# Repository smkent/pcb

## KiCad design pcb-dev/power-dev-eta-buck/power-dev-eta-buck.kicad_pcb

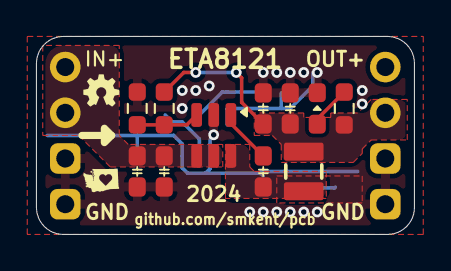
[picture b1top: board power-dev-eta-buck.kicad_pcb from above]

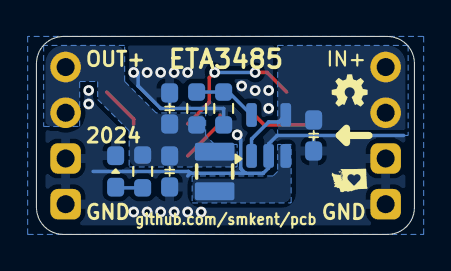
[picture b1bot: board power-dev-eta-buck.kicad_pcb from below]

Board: 2 copper layers, 21.0 x 11.0 mm, 22 parts (11 on the bottom side), 10 nets.

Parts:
C0, C1, C4: 10u; C_0603_1608Metric_Pad1.08x0.95mm_HandSolder
C2, C3, C5, C6: 22u; C_0603_1608Metric_Pad1.08x0.95mm_HandSolder
C7: 10n; C_0603_1608Metric_Pad1.08x0.95mm_HandSolder
J1, J2: Pin headers; PinHeader_1x04_P2.54mm_Vertical_simple_pad3,4gnd
L1, L2: 4u7; IND-SMD_L2.5-W2.0_MHCHL2520
LED1, LED2: LED_Small; LED_0603_1608Metric_Pad1.05x0.95mm_HandSolder_simple
R1: 56K; R_0603_1608Metric_Pad0.98x0.95mm_HandSolder
R2, R3, R5, R6: 10K; R_0603_1608Metric_Pad0.98x0.95mm_HandSolder
R4: 75K; R_0603_1608Metric_Pad0.98x0.95mm_HandSolder
U1: ETA8121; SOT-23-6_simple
U2: ETA3485; SOT-23-5_simple

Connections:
/SW_B: L2.1, U2.3 (SW)
/SW_F: C7.2, L1.1, U1.6 (SW)
FB_B: R4.1, R5.2, U2.5 (FB)
FB_F: R1.1, R2.2, U1.3 (FB)
GND: C0.2, C1.2, C2.2, C3.2, C4.2, C5.2, C6.2, J1.3, J1.4, J2.3, J2.4, LED1.1 (K), LED2.1 (K), R2.1, R5.1, U1.2 (GND), U2.2 (GND)
unnamed: LED1.2 (A), R3.1
unnamed: LED2.2 (A), R6.1
unnamed: C7.1, U1.1 (BST)
VIN: C0.1, C1.1, C4.1, J1.1, J1.2, U1.4 (EN), U1.5 (VIN), U2.1 (EN), U2.4 (IN)
VOUT: C2.1, C3.1, C5.1, C6.1, J2.1, J2.2, L1.2, L2.2, R1.2, R3.2, R4.2, R6.2

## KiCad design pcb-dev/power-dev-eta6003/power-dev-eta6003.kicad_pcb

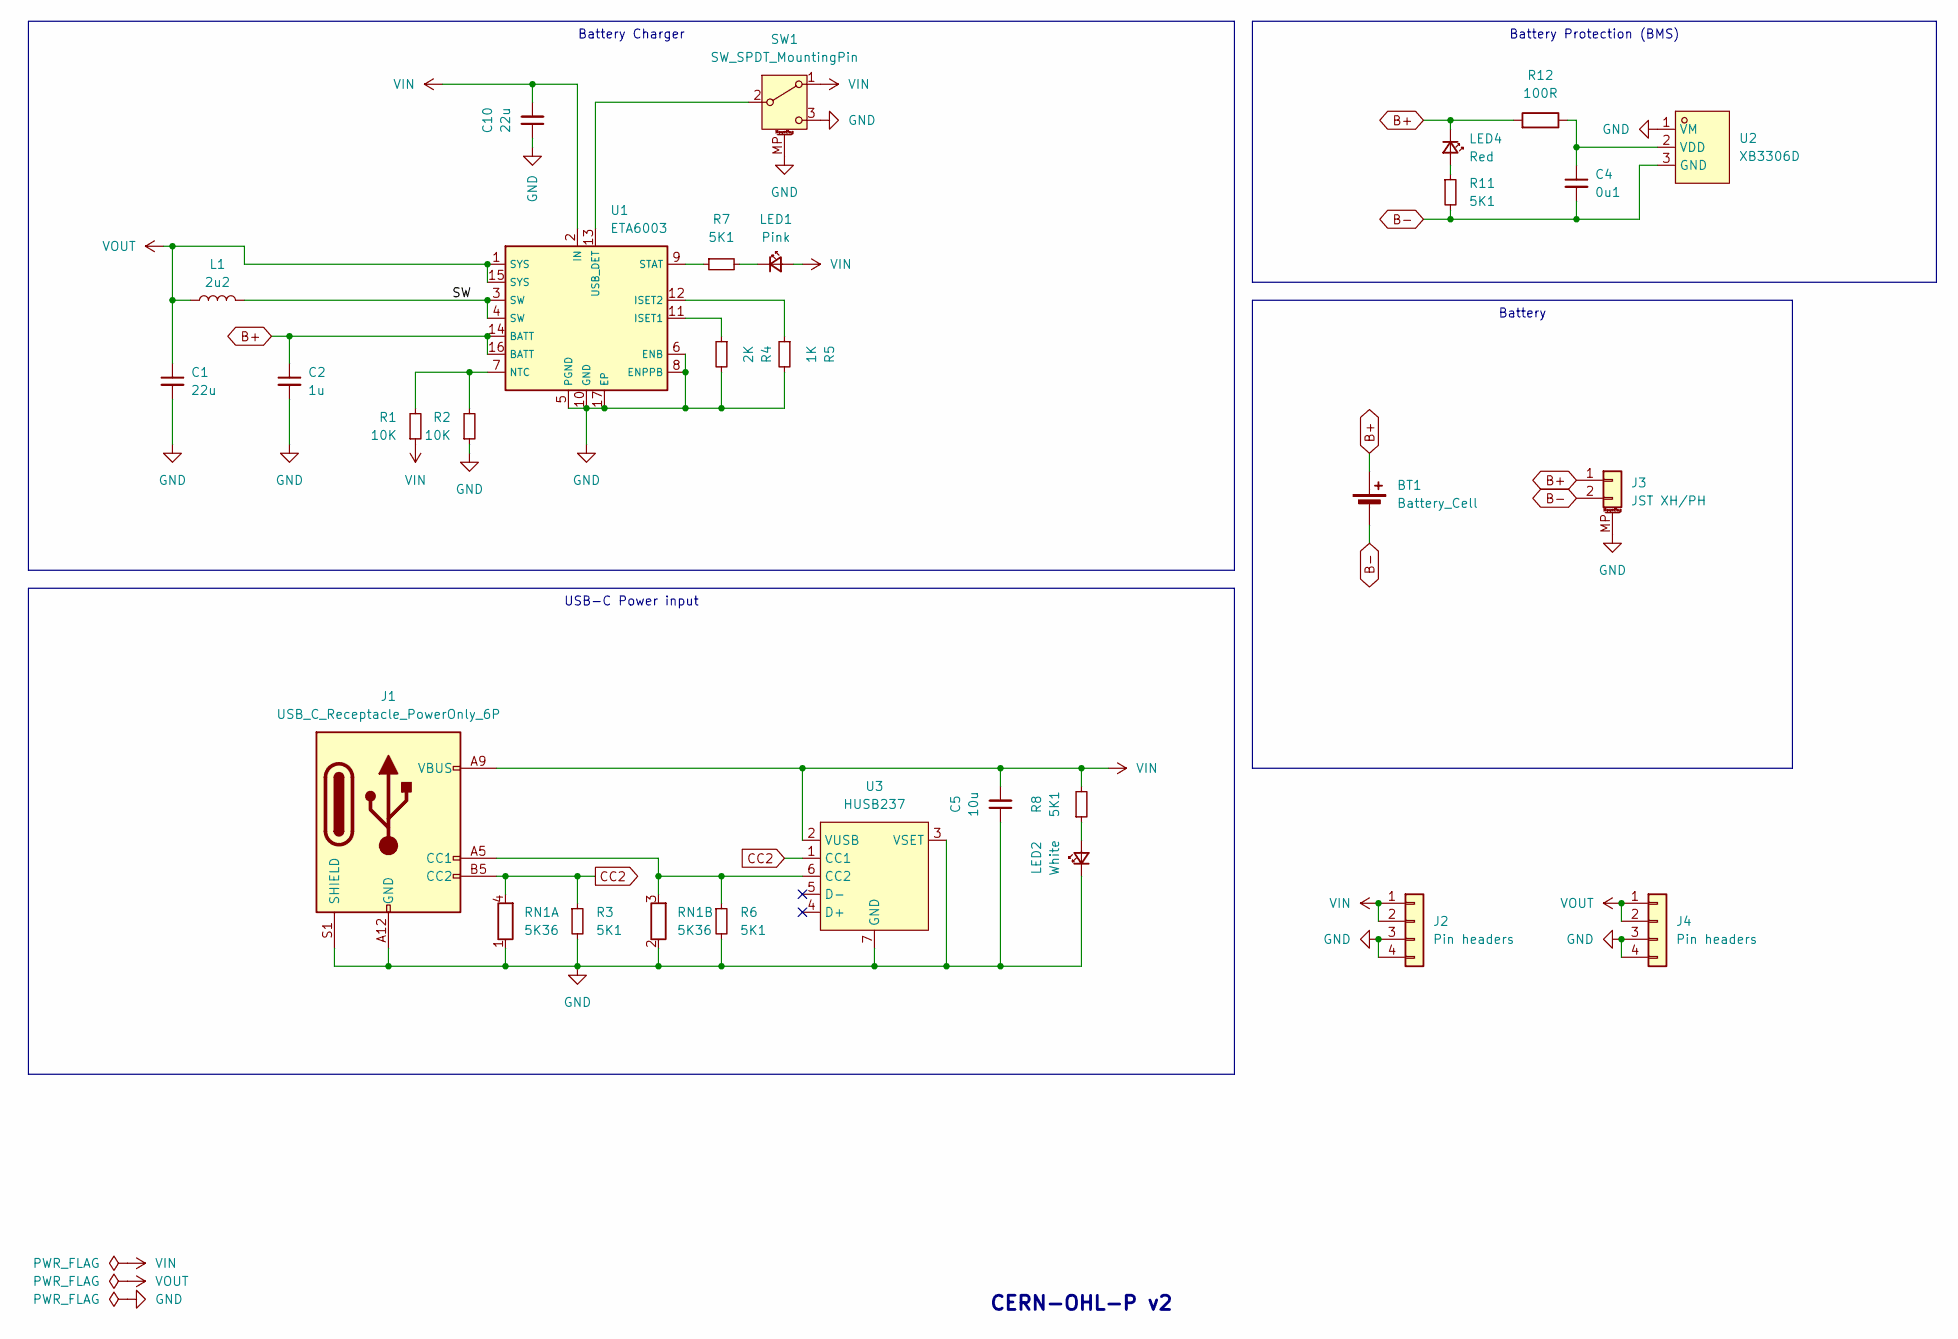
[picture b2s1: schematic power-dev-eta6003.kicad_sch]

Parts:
BT1: Battery_Cell; BAT-TH_18650-A5BJ001
C1: 22u; C_0603_1608Metric_Pad1.08x0.95mm_HandSolder; LCSC Part C45783
C2: 1u; C_0603_1608Metric_Pad1.08x0.95mm_HandSolder; LCSC Part C52923
C4: 0u1; C_0603_1608Metric_Pad1.08x0.95mm_HandSolder; LCSC Part C1525
C5: 10u; C_0603_1608Metric_Pad1.08x0.95mm_HandSolder; LCSC Part C15850
C10: 22u; C_0805_2012Metric_Pad1.18x1.45mm_wide-center_HandSolder; LCSC Part C15850
J1: USB_C_Receptacle_PowerOnly_6P; USB_C_Receptacle_GCT_USB4125-xx-x_6P_TopMnt_Horizontal_hand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; LCSC Part C2927029
J2, J4: Pin headers; PinHeader_1x04_P2.54mm_Vertical_simple_pad3,4gnd
J3: JST XH/PH; Conn_Combo_JST-1x02-XH_PH-SMD-alt-pad2gnd
L1: 2u2; IND-SMD_L2.5-W2.0_MHCHL2520; LCSC Part C5832372
LED1: Pink; LED_0603_1608Metric_Pad1.05x0.95mm_HandSolder_simple
LED2: White; LED_0603_1608Metric_Pad1.05x0.95mm_HandSolder_simple
LED4: Red; LED_0603_1608Metric_Pad1.05x0.95mm_HandSolder_simple; LCSC Part C2286
R1, R2: 10K; R_0603_1608Metric_Pad0.98x0.95mm_HandSolder_simple; LCSC Part C25744
R3, R6, R11: 5K1; R_0603_1608Metric_Pad0.98x0.95mm_HandSolder_simple; LCSC Part C25905
R4: 2K; R_0603_1608Metric_Pad0.98x0.95mm_HandSolder; LCSC Part C22975
R5: 1K; R_0603_1608Metric_Pad0.98x0.95mm_HandSolder; LCSC Part C21190
R7, R8: 5K1; R_0603_1608Metric_Pad0.98x0.95mm_HandSolder_simple; LCSC Part C21190
R12: 100R; R_0603_1608Metric_Pad0.98x0.95mm_HandSolder_simple; LCSC Part C25076
RN1: 5K36; R_Array_Convex_2x0402
SW1: SW_SPDT_MountingPin; SW-SMD_3P-P1.50_L2.7-W6.6
U1: ETA6003; ETA6003_QFN-16-1EP_3x3mm_P0.5mm_EP1.7x1.7mm_ThermalVias; LCSC Part C5455585
U2: XB3306D; SOT-23_simple; LCSC Part C2759992
U3: HUSB237; DFN-6-1EP_2x2mm_P0.65mm_EP1x1.6mm; LCSC Part C7471904

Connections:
/SW: L1.2, U1.3 (SW), U1.4 (SW)
B+: BT1.1 (+), C2.1, J3.1, LED4.1 (K), R12.2, U1.14 (BATT), U1.16 (BATT)
B-: BT1.2 (-), C4.2, J3.2, R11.2, U2.3 (GND)
CC2: J1.B5 (CC2), R3.1, RN1.4 (R1.2), U3.1 (CC1)
GND: C1.2, C2.2, C5.1, C10.1, J1.A12 (GND), J1.B12 (GND), J1.S1 (SHIELD), J2.3, J2.4, J3.MP (MountPin), J4.3, J4.4, LED2.1 (K), R2.1, R3.2, R4.2, R5.2, R6.2, RN1.1 (R1.1), RN1.2 (R2.1), SW1.3 (C), SW1.MP (MountPin), U1.5 (PGND), U1.6 (ENB), U1.8 (ENPPB), U1.10 (GND), U1.17 (EP), U2.1 (VM), U3.3 (VSET), U3.7 (GND)
unnamed: J1.A5 (CC1), R6.1, RN1.3 (R2.2), U3.6 (CC2)
unnamed: LED1.1 (K), R7.2
unnamed: LED2.2 (A), R8.1
unnamed: LED4.2 (A), R11.1
unnamed: SW1.2 (B), U1.13 (USB_DET)
unnamed: R4.1, U1.11 (ISET1)
unnamed: R5.1, U1.12 (ISET2)
unnamed: R1.2, R2.2, U1.7 (NTC)
unnamed: R7.1, U1.9 (STAT)
unnamed: C4.1, R12.1, U2.2 (VDD)
VIN: C5.2, C10.2, J1.A9 (VBUS), J1.B9 (VBUS), J2.1, J2.2, LED1.2 (A), R1.1, R8.2, SW1.1 (A), U1.2 (IN), U3.2 (VUSB)
VOUT: C1.1, J4.1, J4.2, L1.1, U1.1 (SYS), U1.15 (SYS)

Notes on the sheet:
USB-C Power input
Battery Protection (BMS)
Battery Charger
Battery
CERN-OHL-P v2

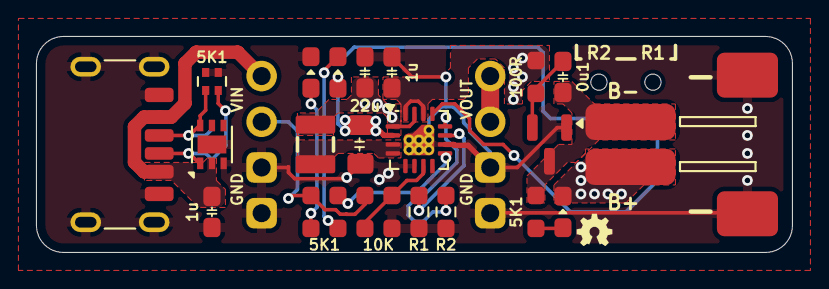
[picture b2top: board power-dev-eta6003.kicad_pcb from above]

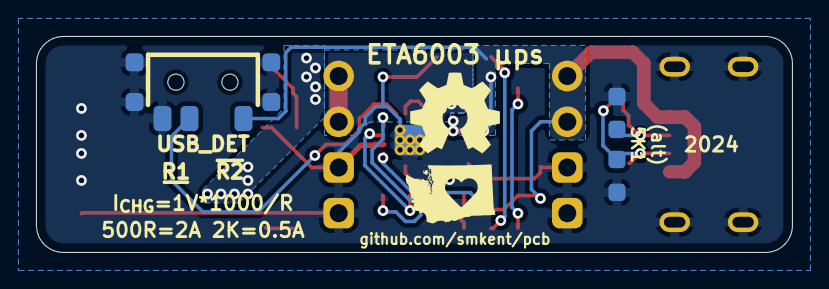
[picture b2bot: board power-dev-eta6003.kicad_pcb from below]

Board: 2 copper layers, 42.0 x 12.0 mm, 28 parts (5 on the bottom side), 17 nets.

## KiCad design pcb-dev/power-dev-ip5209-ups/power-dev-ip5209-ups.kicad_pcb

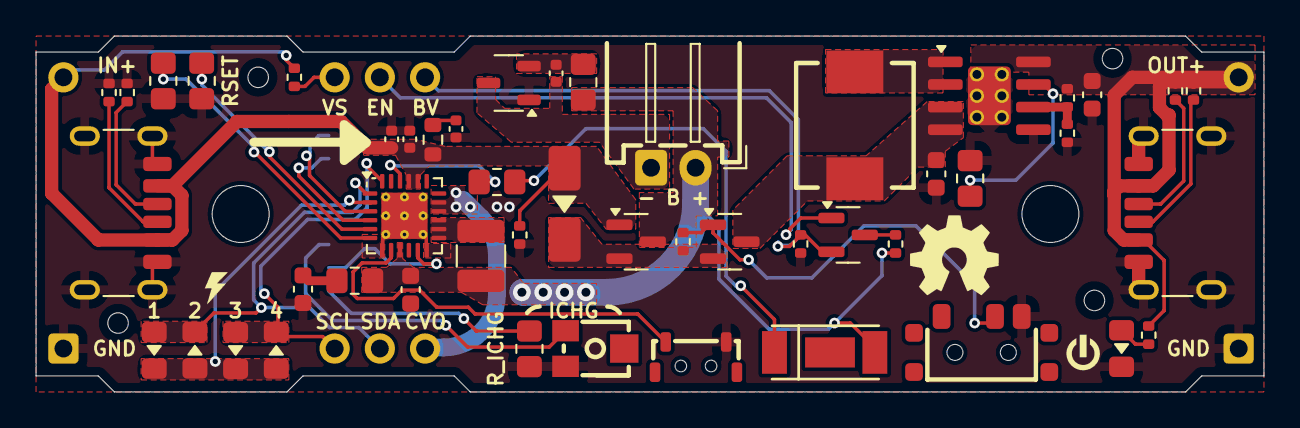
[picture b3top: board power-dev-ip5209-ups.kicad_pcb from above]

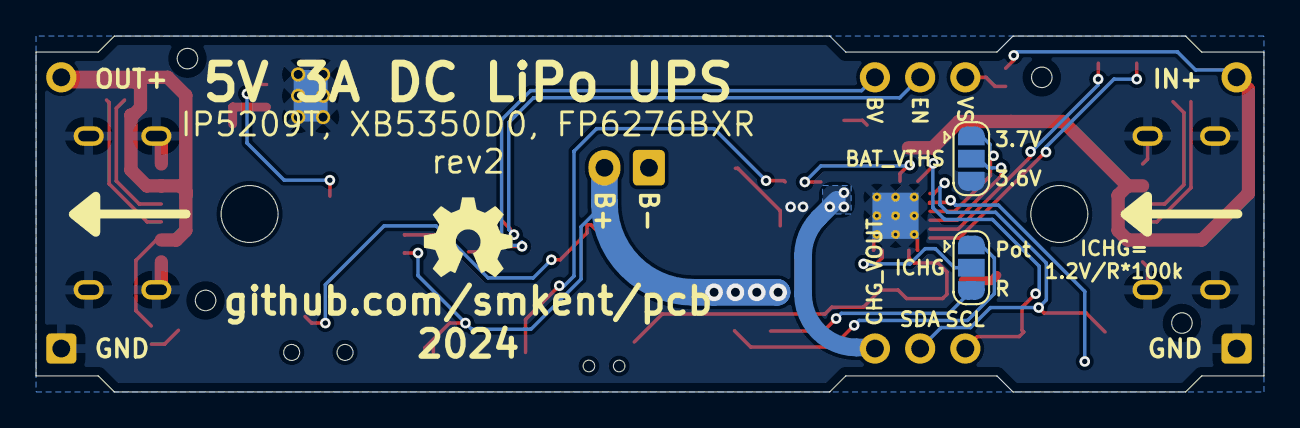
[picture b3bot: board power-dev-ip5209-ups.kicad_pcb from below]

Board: 2 copper layers, 69.0 x 20.0 mm, 57 parts (8 on the bottom side), 38 nets.

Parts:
BT1: Battery_Cell; JST_XH_S2B-XH-2AW_1x02_P2.50mm_pad2gnd_trim
C1, C6: 10uF; C_0402_1005Metric
C2, C7, C10, C11: 22uF; C_0603_1608Metric
C3: 100nF; C_0402_1005Metric
C9: 0.1uF; C_0402_1005Metric
D1: SS34; D_SMA_simple
J1, J2: USB_C_Receptacle_PowerOnly_6P; USB_C_Receptacle_GCT_USB4125-xx-x_6P_TopMnt_Horizontal_hand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
J3, J9: Conn_01x03; PinHeader_1x03_P2.54mm_Vertical_simple
J5, J8: Conn_01x01; PinHeader_1x01_P2.54mm_simple
J11, J12: Conn_01x01; PinHeader_1x01_P2.54mm_simple_square
JP1, JP2: SolderJumper_3_Open; SolderJumper-3_P1.3mm_Open_RoundedPad1.0x1.5mm
L1: 1uH; L_1210_3225Metric
L2: 4.7uH; IND-SMD_L7.0-W6.6
LED1, LED2, LED3, LED4: LED_0805_2012Metric_Pad1.15x1.40mm_HandSolder_simple
LED5: LED-SMD_3P-L5.7-W3.0-RD
LED6: Boost; LED_0805_2012Metric_Pad1.15x1.40mm_HandSolder_simple
Q1, Q2: AO3401A; SOT-23
Q3: BSS138; SOT-23
R1: 120K; R_0805_2012Metric_Pad1.20x1.40mm_HandSolder
R2: 20R; R_0805_2012Metric_Pad1.20x1.40mm_HandSolder
R3: 2R; R_0603_1608Metric
R4: 0R5; R_0805_2012Metric_Pad1.20x1.40mm_HandSolder
R5: 100R; R_0805_2012Metric_Pad1.20x1.40mm_HandSolder
R6, R7, R9, R10, R13, R14, R15, R16, R17: 10K; R_0402_1005Metric
R8: 75K; R_0402_1005Metric
R11, R12: 5K1; R_0402_1005Metric
R18: 10K; R_0805_2012Metric_Pad1.20x1.40mm_HandSolder
R19: 47K; R_0805_2012Metric_Pad1.20x1.40mm_HandSolder
R20: 0R; R_0805_2012Metric_Pad1.20x1.40mm_HandSolder
RV1: R_Potentiometer_US; RES-ADJ-SMD_VG039NCH
SW1: SW_Push; SW-SMD_BZCN_TSA002A35XXX
SW2: SW_SPDT; SW-SMD_3P-P1.50_L2.7-W6.6
U1: IP5209T; QFN-24-1EP_4x4mm_P0.5mm_EP2.6x2.6mm_ThermalVias
U2: XB3306D; SOT-23-3
U3: FP6276BXR-G1; SOIC-8-1EP_3.9x4.9mm_P1.27mm_EP2.41x3.3mm_ThermalVias_Custo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

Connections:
B+: BT1.1 (+), C2.1, L1.2, LED5.2 (A), Q1.3 (D), R4.1, R5.1, R15.1, U1.9 (BAT)
B-: BT1.2 (-), C9.1, U2.3 (GND)
BATVDD: C9.2, R5.2, U2.2 (VDD)
BAT_SENSE: J9.1, Q3.2 (S), R16.1
BAT_SENSE_ENABLE: J9.2, Q3.1 (G)
BOOST: C10.1, L2.1, Q2.3 (D), U3.3 (VIN), U3.4 (EN)
BOOST_OC: R19.2, U3.7 (OC)
BOOST_SW: L2.2, U3.1 (LX), U3.2 (LX)
CHARGE_VOUT: J3.3, U1.16 (VOUT), U1.17 (VOUT)
FB: R8.2, R9.1, U3.6 (FB)
GND: C1.2, C2.2, C3.2, C6.2, C7.2, C10.2, C11.2, J1.A12 (GND), J1.B12 (GND), J1.S1 (SHIELD), J2.A12 (GND), J2.B12 (GND), J2.S1 (SHIELD), J11.1, J12.1, JP1.3 (B), LED6.1 (K), R1.2, R6.2, R9.2, R11.2, R12.2, R16.2, R18.2, R19.1, R20.1, RV1.3, SW1.1, SW2.3 (C), U1.7 (AGND), U1.12 (PGND), U1.25 (EP), U2.1 (VM), U3.5 (GND), U3.9 (EP)
ICHG: JP2.2 (C), U1.11 (ICHG)
KEY: SW1.2, U1.8 (KEY)
LED1: J3.1, LED3.2 (A), LED4.1 (K), U1.24 (L1)
LED2: J3.2, LED1.2 (A), LED2.1 (K), U1.1 (L2)
LED3: LED1.1 (K), LED2.2 (A), LED3.1 (K), LED4.2 (A), U1.2 (L3)
LIGHT: R2.1, U1.22 (LIGHT)
LOAD_SWITCH: D1.1 (K), Q1.2 (S), Q2.2 (S), R7.1
unnamed: C6.1, R3.2
unnamed: C7.1, R4.2
unnamed: J1.A5 (CC1), R12.1
unnamed: J1.B5 (CC2), R11.1
unnamed: J2.A5 (CC1), R13.2
unnamed: J2.B5 (CC2), R14.2
unnamed: JP2.1 (A), RV1.1
unnamed: JP2.3 (B), R1.1
unnamed: LED5.1 (K), R2.2
unnamed: LED6.2 (A), R10.2
unnamed: Q2.1 (G), R7.2, SW2.2 (B)
unnamed: Q3.3 (D), R15.2
unnamed: R20.2, U1.6 (NTC)
POWER_IN_SENSE: J9.3, R17.2
RSET: R18.1, U1.5 (RSET)
SW: L1.1, U1.13 (LX), U1.14 (LX), U1.15 (LX)
VIN: C1.1, C3.1, D1.2 (A), J1.A9 (VBUS), J1.B9 (VBUS), J5.1, Q1.1 (G), R3.1, R6.1, R17.1, U1.20 (VIN), U1.21 (VIN)
VOUT: C11.1, J2.A9 (VBUS), J2.B9 (VBUS), J8.1, R8.1, R10.1, R13.1, R14.1, U3.8 (VO)
VREG: JP1.1 (A), U1.3 (VREG)
VTHS: JP1.2 (C), U1.4 (VTHS)

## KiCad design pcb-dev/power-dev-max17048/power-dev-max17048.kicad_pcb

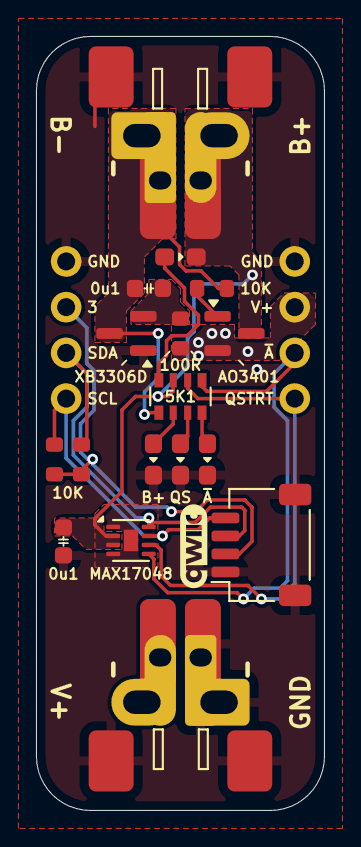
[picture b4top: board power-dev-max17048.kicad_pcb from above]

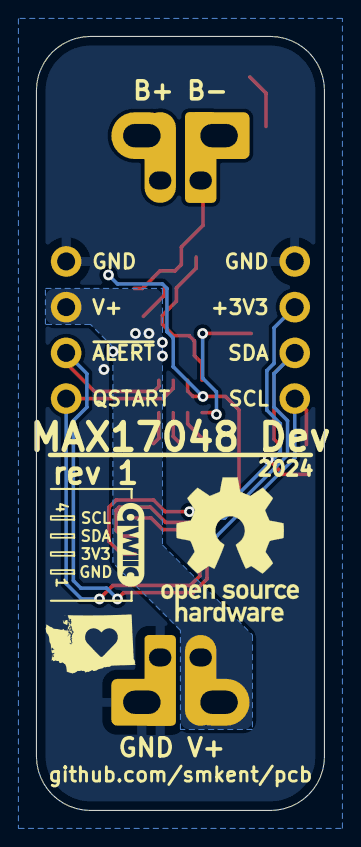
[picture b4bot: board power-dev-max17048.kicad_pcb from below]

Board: 2 copper layers, 16.0 x 43.0 mm, 19 parts (2 on the bottom side), 15 nets.

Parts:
C1, C2: 0u1; C_0603_1608Metric
J1: Qwiic; Qwiic-SMD-horizontal-logo-bottom-pinout
J2, J5: JST XH / PH / screw terminal; Conn_Combo_TerminalBlock_JST-1x02-XH_PH-pad2gnd
J3, J4: Pin headers; PinHeader_1x04_P2.54mm_Vertical_simple
LED1: Red; LED_0603_1608Metric_Pad1.05x0.95mm_HandSolder_simple
LED2: Green; LED_0603_1608Metric_Pad1.05x0.95mm_HandSolder_simple
LED3: White; LED_0603_1608Metric_Pad1.05x0.95mm_HandSolder_simple
LED4: Pink; LED_0603_1608Metric_Pad1.05x0.95mm_HandSolder_simple
Q1: AO3401A; SOT-23_simple
R1: 100R; R_0603_1608Metric_simple
R2, R3, R4: 10K; R_0603_1608Metric_simple
RN1: 5K1; R_Array_Convex_4x0603
U1: MAX17048; TDFN-8-1EP_2x2mm_P0.5mm_EP0.8x1.2mm
U2: XB3306D; SOT-23_simple

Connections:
+3V3: J1.2 (+3V3), J3.2, R2.1, R3.1
/PROTECT_VDD: C2.1, R1.1, U2.2 (VDD)
B+: C1.1, J2.1, LED1.1 (K), Q1.3 (D), RN1.7 (R2.2), U1.2 (CELL), U1.3 (V_{DD})
B-: C2.2, J2.2, R4.2, RN1.1 (R1.1), U2.3 (GND)
GND: C1.2, J1.1 (GND), J1.MP, J2.MP (MountPin), J3.1, J4.1, J5.2, J5.MP (MountPin), LED2.1 (K), LED3.1 (K), LED4.1 (K), U1.1 (CTG), U1.4 (GND), U1.9 (EP), U2.1 (VM)
unnamed: LED1.2 (A), RN1.8 (R1.2)
unnamed: LED2.2 (A), RN1.2 (R2.1)
unnamed: LED3.2 (A), RN1.3 (R3.1)
unnamed: LED4.2 (A), RN1.4 (R4.1)
unnamed: Q1.1 (G), R4.1
QSTART: J4.4, RN1.6 (R3.2), U1.6 (QSTRT)
SCL: J1.4 (SCL), J3.4, R3.2, U1.7 (SCL)
SDA: J1.3 (SDA), J3.3, R2.2, U1.8 (SDA)
VCC: J4.2, J5.1, Q1.2 (S), R1.2
~ALERT: J4.3, RN1.5 (R4.2), U1.5 (~ALRT)

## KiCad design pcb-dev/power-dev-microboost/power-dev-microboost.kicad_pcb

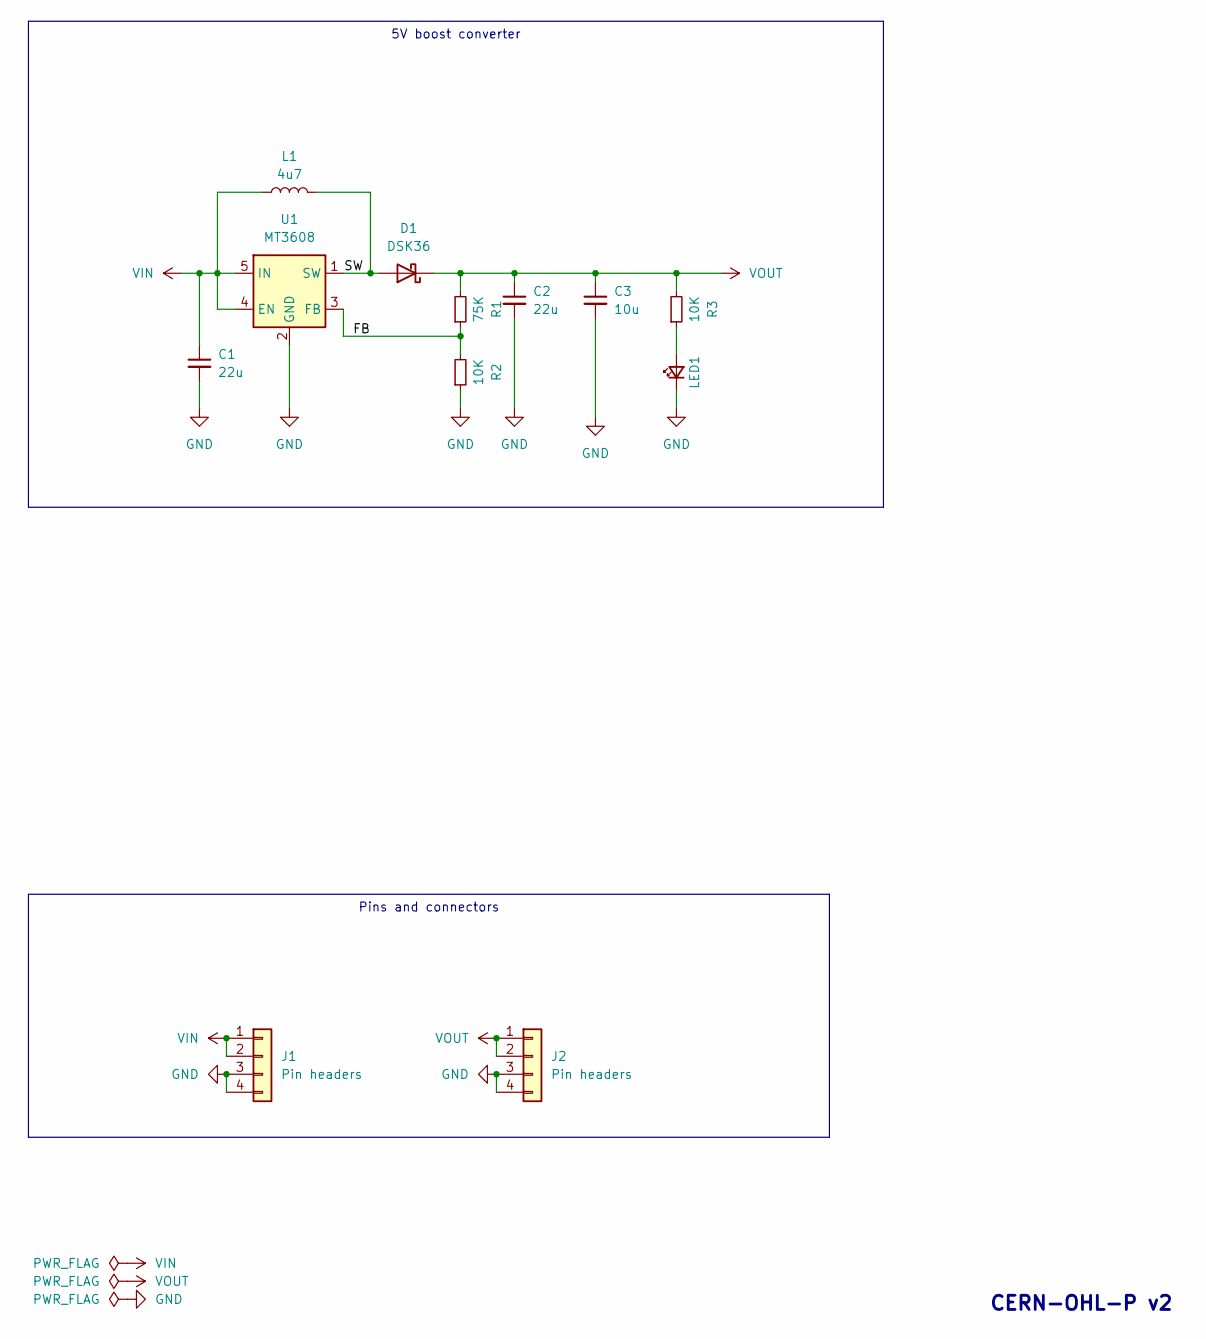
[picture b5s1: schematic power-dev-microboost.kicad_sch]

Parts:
C1, C2: 22u; C_0805_2012Metric_Pad1.18x1.45mm_HandSolder
C3: 10u; C_0603_1608Metric_Pad1.08x0.95mm_HandSolder
D1: DSK36; D_SOD-123F_simple
J1, J2: Pin headers; PinHeader_1x04_P2.54mm_Vertical_simple
L1: 4u7; IND-SMD_L2.5-W2.0_MHCHL2520
LED1: LED_Small; LED_0603_1608Metric_Pad1.05x0.95mm_HandSolder_simple
R1: 75K; R_0603_1608Metric_Pad0.98x0.95mm_HandSolder
R2, R3: 10K; R_0603_1608Metric_Pad0.98x0.95mm_HandSolder
U1: MT3608; SOT-23-6; LCSC Part C84817

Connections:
/FB: R1.1, R2.2, U1.3 (FB)
/SW: D1.2 (A), L1.2, U1.1 (SW)
GND: C1.2, C2.2, C3.2, J1.3, J1.4, J2.3, J2.4, LED1.1 (K), R2.1, U1.2 (GND)
unnamed: LED1.2 (A), R3.1
VIN: C1.1, J1.1, J1.2, L1.1, U1.4 (EN), U1.5 (IN)
VOUT: C2.1, C3.1, D1.1 (K), J2.1, J2.2, R1.2, R3.2

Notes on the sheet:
Pins and connectors
5V boost converter
CERN-OHL-P v2

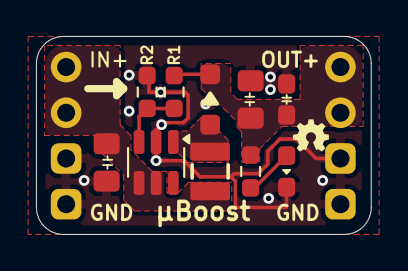
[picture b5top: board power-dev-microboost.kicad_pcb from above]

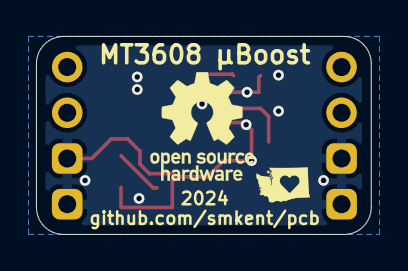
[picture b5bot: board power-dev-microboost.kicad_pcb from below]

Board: 2 copper layers, 18.6 x 11.0 mm, 12 parts (2 on the bottom side), 6 nets.

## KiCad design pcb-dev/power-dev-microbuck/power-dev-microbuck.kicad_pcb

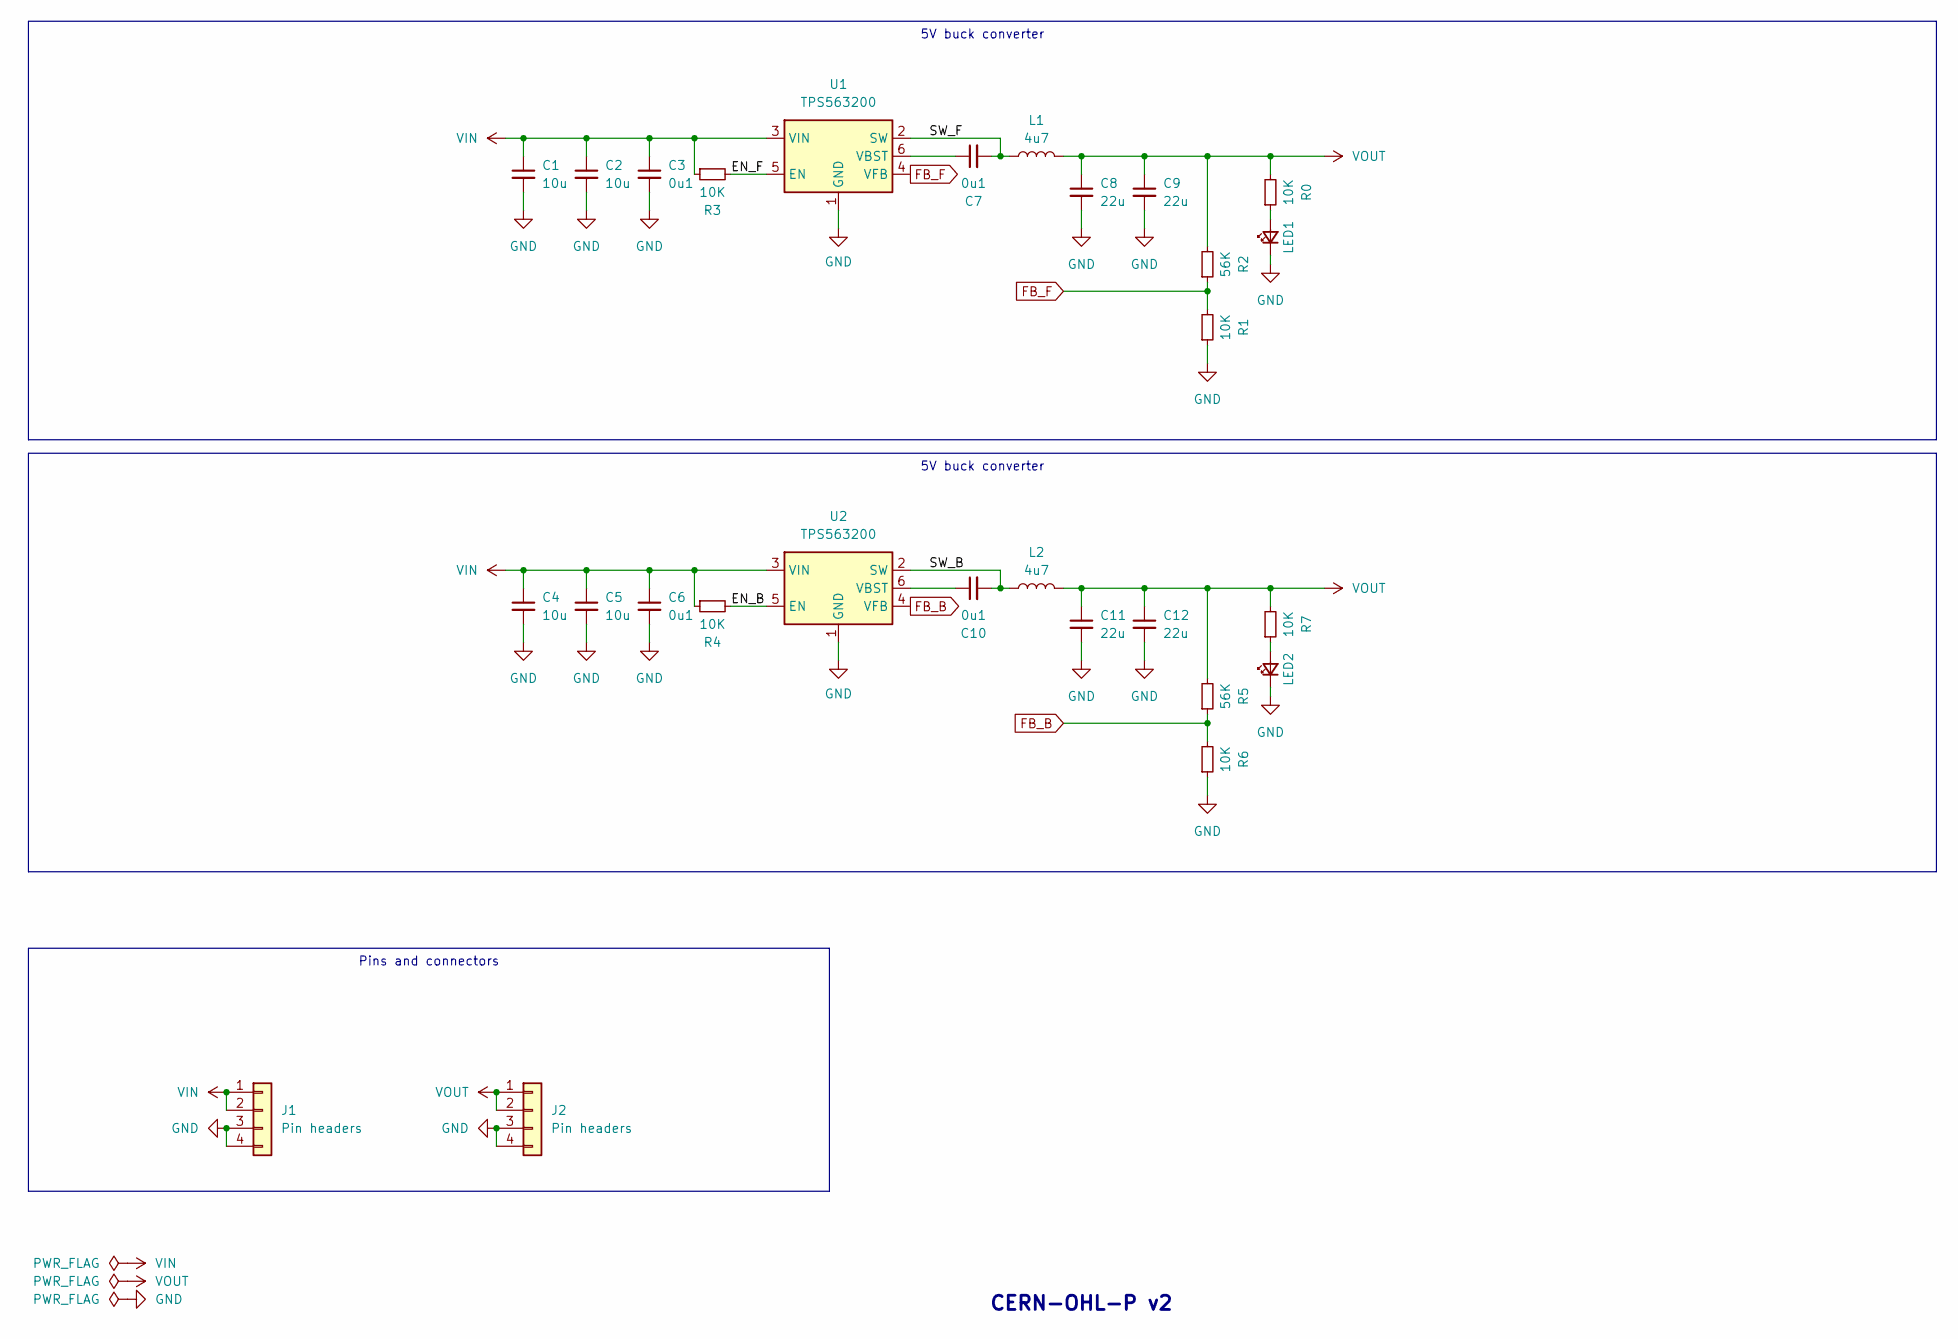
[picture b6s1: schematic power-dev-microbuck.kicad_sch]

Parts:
C1, C2, C4, C5: 10u; C_0603_1608Metric_Pad1.08x0.95mm_HandSolder
C3, C6, C7, C10: 0u1; C_0603_1608Metric_Pad1.08x0.95mm_HandSolder
C8, C9, C11, C12: 22u; C_0603_1608Metric_Pad1.08x0.95mm_HandSolder
J1, J2: Pin headers; PinHeader_1x04_P2.54mm_Vertical_simple
L1, L2: 4u7; IND-SMD_L2.5-W2.0_MHCHL2520
LED1, LED2: LED_Small; LED_0603_1608Metric_Pad1.05x0.95mm_HandSolder_simple
R0, R1, R3, R4, R6, R7: 10K; R_0603_1608Metric_Pad0.98x0.95mm_HandSolder
R2, R5: 56K; R_0603_1608Metric_Pad0.98x0.95mm_HandSolder
U1, U2: TPS563200; SOT-23-6_Handsoldering_simple

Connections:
/EN_B: R4.2, U2.5 (EN)
/EN_F: R3.2, U1.5 (EN)
/SW_B: C10.2, L2.1, U2.2 (SW)
/SW_F: C7.2, L1.1, U1.2 (SW)
FB_B: R5.1, R6.2, U2.4 (VFB)
FB_F: R1.2, R2.1, U1.4 (VFB)
GND: C1.2, C2.2, C3.2, C4.2, C5.2, C6.2, C8.2, C9.2, C11.2, C12.2, J1.3, J1.4, J2.3, J2.4, LED1.1 (K), LED2.1 (K), R1.1, R6.1, U1.1 (GND), U2.1 (GND)
unnamed: LED1.2 (A), R0.1
unnamed: LED2.2 (A), R7.1
unnamed: C7.1, U1.6 (VBST)
unnamed: C10.1, U2.6 (VBST)
VIN: C1.1, C2.1, C3.1, C4.1, C5.1, C6.1, J1.1, J1.2, R3.1, R4.1, U1.3 (VIN), U2.3 (VIN)
VOUT: C8.1, C9.1, C11.1, C12.1, J2.1, J2.2, L1.2, L2.2, R0.2, R2.2, R5.2, R7.2

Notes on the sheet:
Pins and connectors
5V buck converter
CERN-OHL-P v2

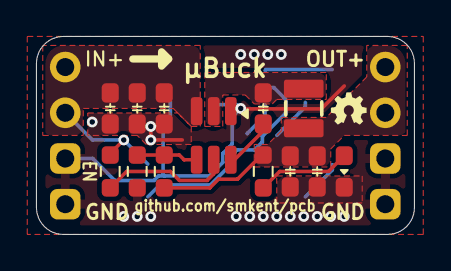
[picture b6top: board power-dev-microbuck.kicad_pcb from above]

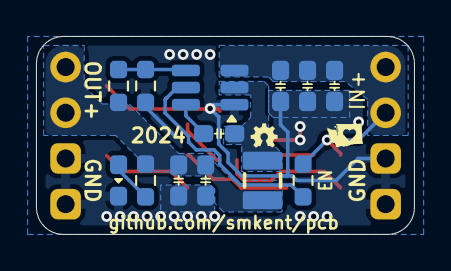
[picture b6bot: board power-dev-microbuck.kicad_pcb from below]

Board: 2 copper layers, 21.0 x 11.0 mm, 28 parts (15 on the bottom side), 13 nets.

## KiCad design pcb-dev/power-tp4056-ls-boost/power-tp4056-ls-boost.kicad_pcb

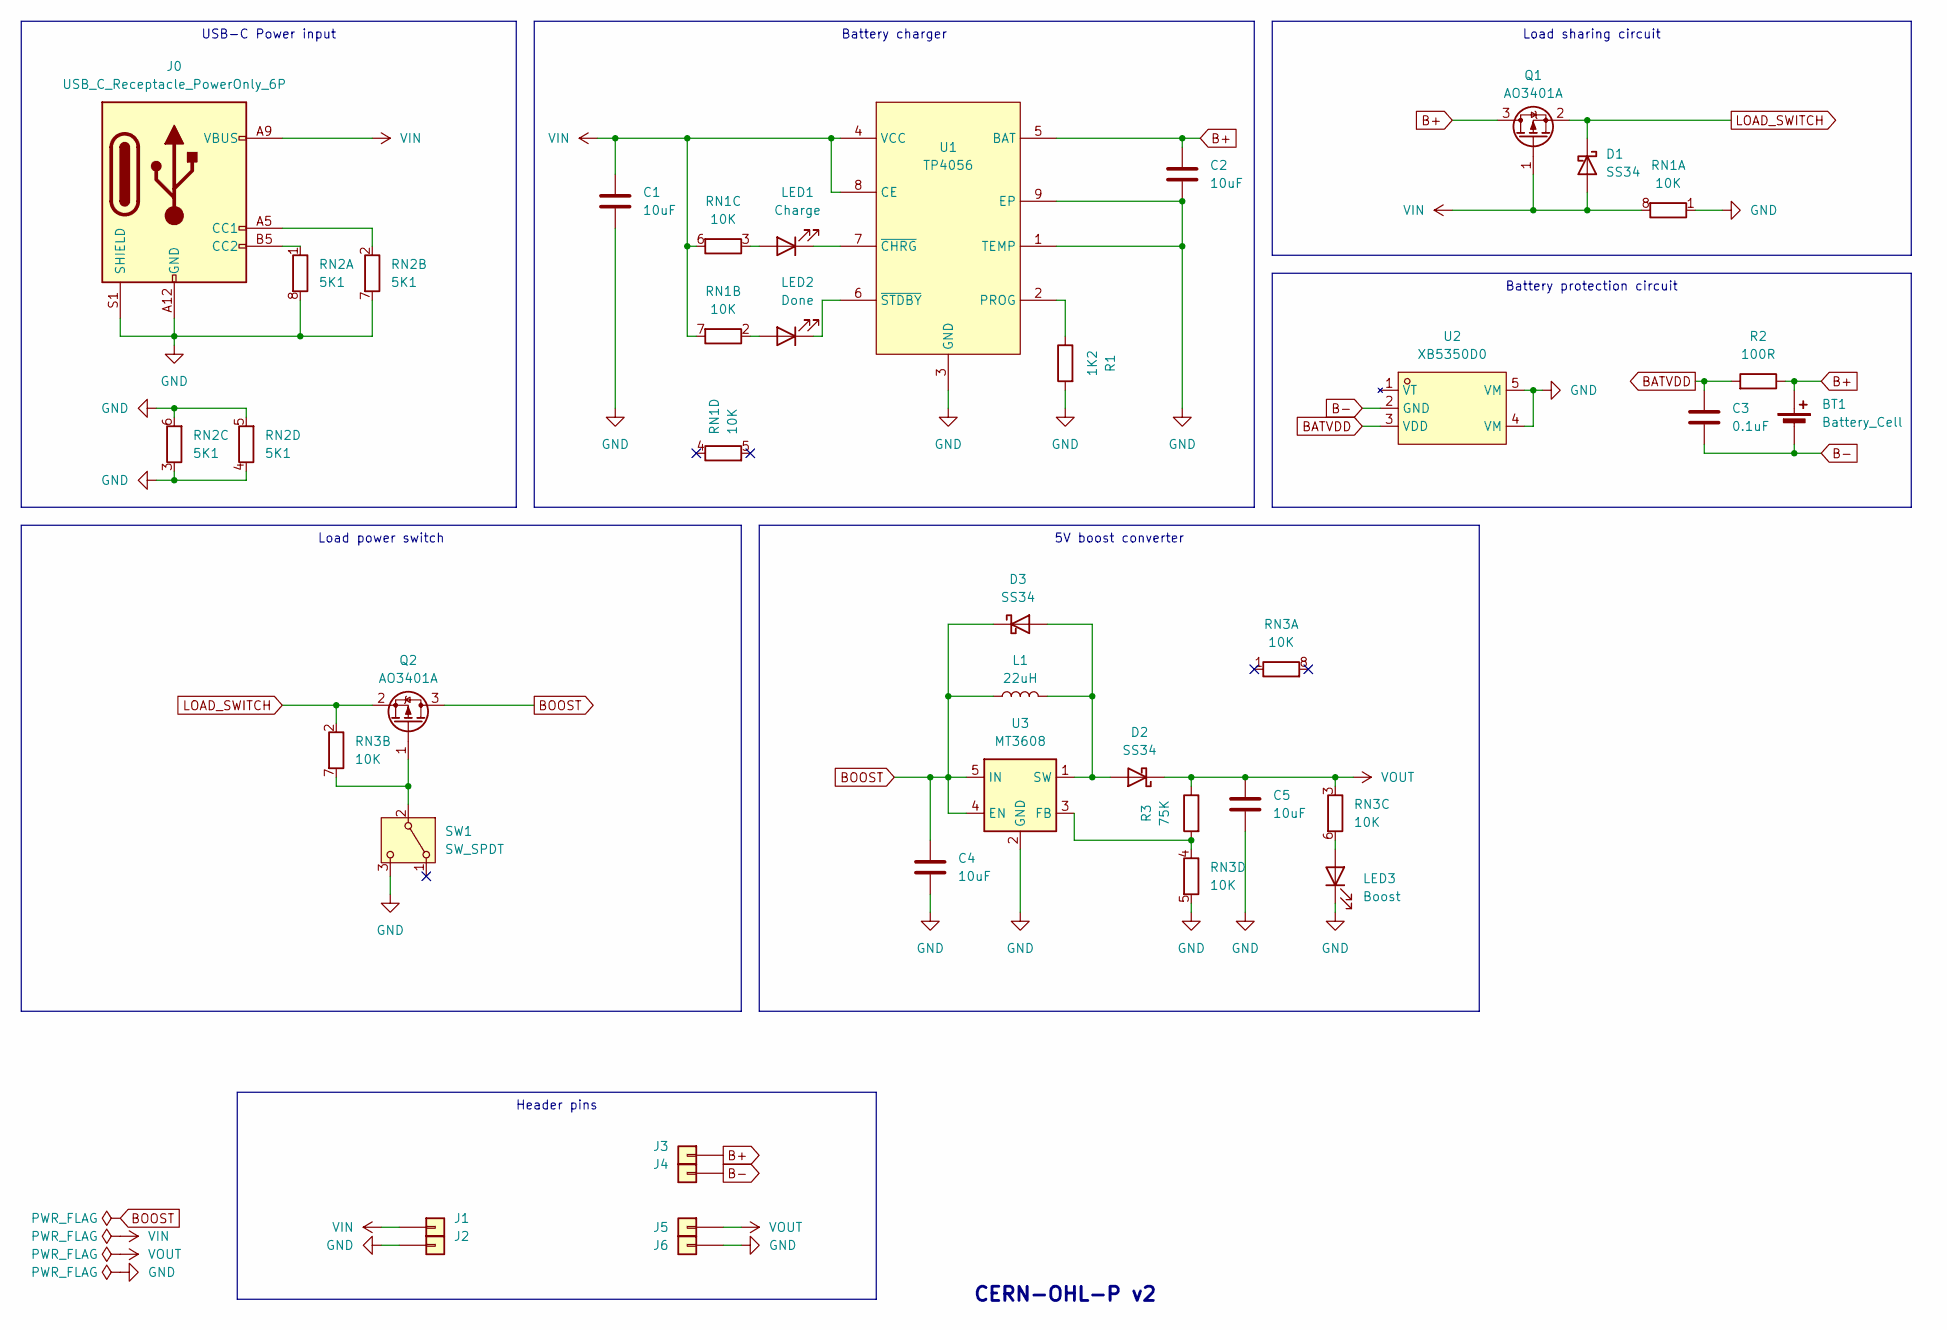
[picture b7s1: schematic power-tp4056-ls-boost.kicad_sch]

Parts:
BT1: Battery_Cell; JST_XH_B2B-XH-A_1x02_P2.50mm_Vertical_simple
C1, C2, C4, C5: 10uF; C_0805_2012Metric_Pad1.18x1.45mm_HandSolder; LCSC Part C15850
C3: 0.1uF; C_0805_2012Metric_Pad1.18x1.45mm_HandSolder; LCSC Part C28233
D1, D2, D3: SS34; D_SMA_simple; LCSC Part C8678
J0: USB_C_Receptacle_PowerOnly_6P; USB_C_Receptacle_GCT_USB4125-xx-x_6P_TopMnt_Horizontal_hand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
J1, J3, J5: Conn_01x01; PinHeader_1x01_P2.54mm_simple
J2, J4, J6: Conn_01x01; PinHeader_1x01_P2.54mm_simple_square
L1: 22uH; IND-SMD_L7.0-W6.6; LCSC Part C5832376
LED1: Charge; LED_0805_2012Metric_Pad1.15x1.40mm_HandSolder_simple
LED2: Done; LED_0805_2012Metric_Pad1.15x1.40mm_HandSolder_simple
LED3: Boost; LED_0805_2012Metric_Pad1.15x1.40mm_HandSolder_simple
Q1, Q2: AO3401A; SOT-23; LCSC Part C15127
R1: 1K2; R_0805_2012Metric_Pad1.20x1.40mm_HandSolder; LCSC Part C17379
R2: 100R; R_0805_2012Metric_Pad1.20x1.40mm_HandSolder; LCSC Part C17408
R3: 75K; R_0805_2012Metric_Pad1.20x1.40mm_HandSolder
RN1, RN3: 10K; R_Array_Convex_4x0603; LCSC Part C29718
RN2: 5K1; R_Array_Convex_4x0603
SW1: SW_SPDT; SW-TH_DEALON_SS-12D01-GX_simple; LCSC Part C2998803
U1: TP4056; SOIC-8-1EP_3.9x4.9mm_P1.27mm_EP2.41x3.3mm_ThermalVias_Custo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; JLCPCB_CORRECTION 0; 0; 270
U2: XB5350D0; SOT-23-5_simple; JLCPCB_CORRECTION 0; 0; 270
U3: MT3608; SOT-23-6; LCSC Part C84817

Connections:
B+: BT1.1 (+), C2.2, J3.1, Q1.3 (D), R2.1, U1.5 (BAT)
B-: BT1.2 (-), C3.1, J4.1, U2.2 (GND)
BATVDD: C3.2, R2.2, U2.3 (VDD)
BOOST: C4.1, D3.1 (K), L1.1, Q2.3 (D), U3.4 (EN), U3.5 (IN)
GND: C1.2, C2.1, C4.2, C5.2, J0.A12 (GND), J0.B12 (GND), J0.S1 (SHIELD), J2.1, J6.1, LED3.1 (K), R1.2, RN1.1 (R1.1), RN2.3 (R3.1), RN2.4 (R4.1), RN2.5 (R4.2), RN2.6 (R3.2), RN2.7 (R2.2), RN2.8 (R1.2), RN3.5 (R4.2), SW1.3 (C), U1.1 (TEMP), U1.3 (GND), U1.9 (EP), U2.4 (VM), U2.5 (VM), U3.2 (GND)
LOAD_SWITCH: D1.1 (K), Q1.2 (S), Q2.2 (S), RN3.2 (R2.1)
unnamed: D2.2 (A), D3.2 (A), L1.2, U3.1 (SW)
unnamed: J0.A5 (CC1), RN2.2 (R2.1)
unnamed: J0.B5 (CC2), RN2.1 (R1.1)
unnamed: LED1.2 (A), RN1.3 (R3.1)
unnamed: LED1.1 (K), U1.7 (~CHRG)
unnamed: LED2.2 (A), RN1.2 (R2.1)
unnamed: LED2.1 (K), U1.6 (~STDBY)
unnamed: LED3.2 (A), RN3.6 (R3.2)
unnamed: Q2.1 (G), RN3.7 (R2.2), SW1.2 (B)
unnamed: R3.2, RN3.4 (R4.1), U3.3 (FB)
unnamed: R1.1, U1.2 (PROG)
VIN: C1.1, D1.2 (A), J0.A9 (VBUS), J0.B9 (VBUS), J1.1, Q1.1 (G), RN1.6 (R3.2), RN1.7 (R2.2), RN1.8 (R1.2), U1.4 (VCC), U1.8 (CE)
VOUT: C5.1, D2.1 (K), J5.1, R3.1, RN3.3 (R3.1)

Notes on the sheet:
Header pins
Battery protection circuit
USB-C Power input
Load sharing circuit
Load power switch
Battery charger
5V boost converter
CERN-OHL-P v2

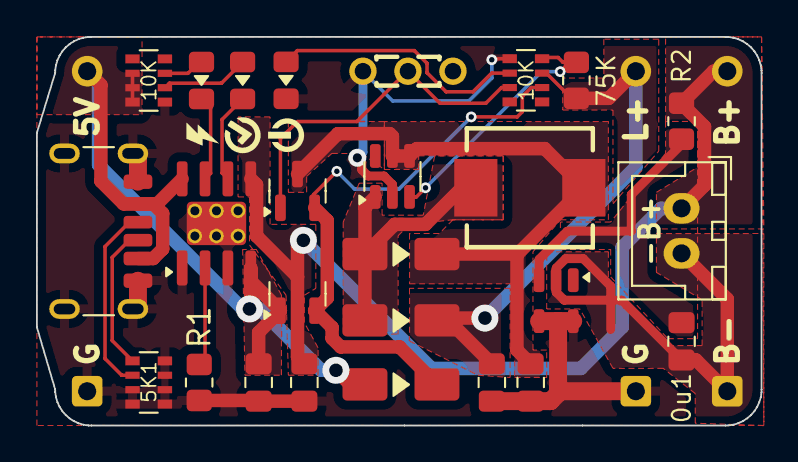
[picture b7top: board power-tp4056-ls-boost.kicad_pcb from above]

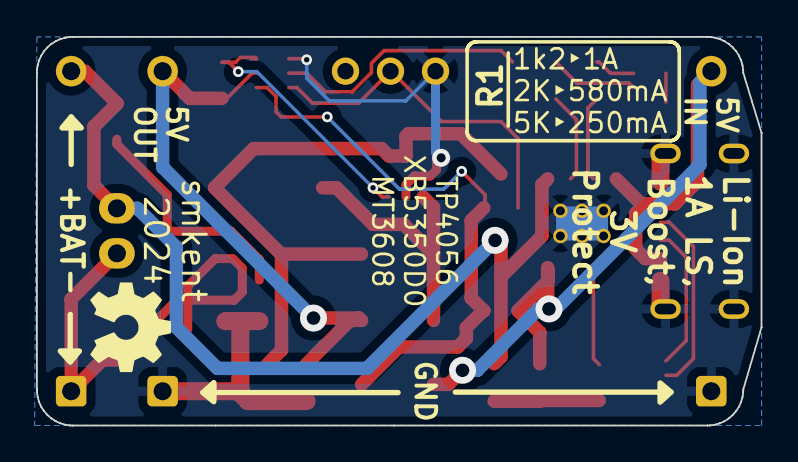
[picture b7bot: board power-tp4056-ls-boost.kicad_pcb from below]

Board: 2 copper layers, 40.3 x 21.6 mm, 32 parts (6 on the bottom side), 19 nets.
